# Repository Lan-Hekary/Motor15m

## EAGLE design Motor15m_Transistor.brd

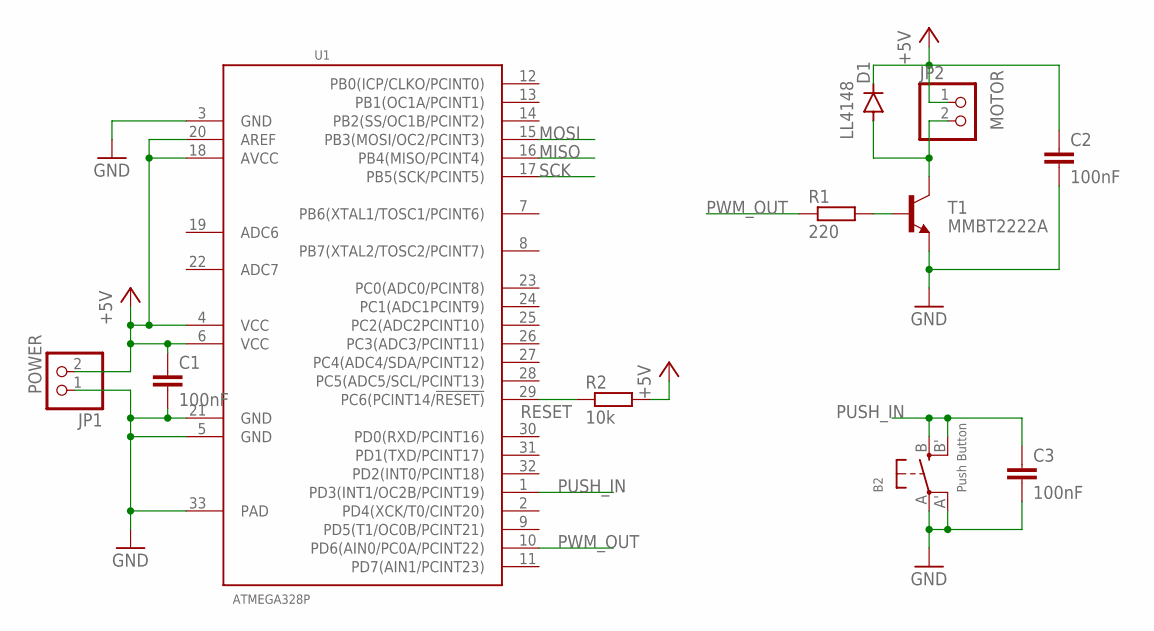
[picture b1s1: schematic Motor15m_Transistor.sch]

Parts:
B2: Push Button; EVQ-Q2
C1, C2, C3: 100nF; C0805
D1: LL4148; SOD80C
JP1: POWER; 1X02/90
JP2: MOTOR; 1X02/90
R1: 220; R0603
R2: 10k; R0603
T1: MMBT2222A; SOT23-BEC
U1: ATMEGA328P; QFN32G-0.5-5X5MM

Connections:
+5V: C1.1, C2.1, D1.C, JP1.2, JP2.1, R2.2, U1.4 (VCC), U1.6 (VCC), U1.18 (AVCC), U1.20 (AREF)
GND: B2.A, B2.A' (P1), C1.2, C2.2, C3.2, JP1.1, T1.E, U1.3 (GND), U1.5 (GND), U1.21 (GND), U1.33 (PAD)
MISO: U1.16 (PB4(MISO/PCINT4))
MOSI: U1.15 (PB3(MOSI/OC2/PCINT3))
unnamed: R1.2, T1.B
unnamed: D1.A, JP2.2, T1.C
PUSH_IN: B2.B (S), B2.B' (S1), C3.1, U1.1 (PD3(INT1/OC2B/PCINT19))
PWM_OUT: R1.1, U1.10 (PD6(AIN0/PC0A/PCINT22))
RESET: R2.1, U1.29 (PC6(PCINT14/!RESET))
SCK: U1.17 (PB5(SCK/PCINT5))

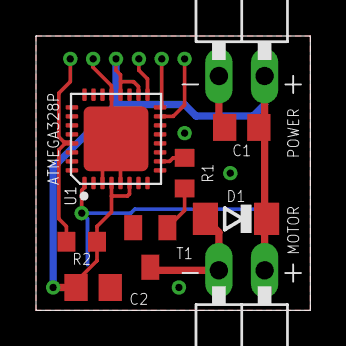
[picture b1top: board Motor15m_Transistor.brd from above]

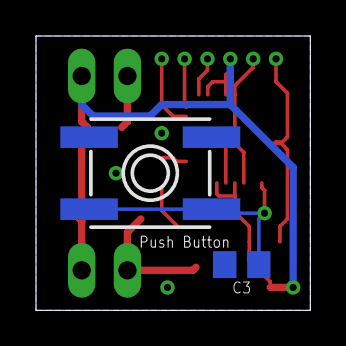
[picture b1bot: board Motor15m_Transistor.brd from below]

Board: 2 copper layers, 15.2 x 15.2 mm, 11 parts (2 on the bottom side), 7 nets.

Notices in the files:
parts and their libraries:
microbuilder: This work is placed in the public domain, and may be freely used for commercial and non-commercial work with the following conditions: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
